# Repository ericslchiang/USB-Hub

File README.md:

## CHIP-8 Emulator by ericslchiang
### March 18th 2025  

######
An USB 2.0 Hub with three downstream USB 2.0 Ports and one SD card slot. Built using a Microchip USB2514B for USB Hub control and a Genesys Logic GL823K USB 2.0 to SD card converter IC.  
Routed on a 4-layer PCB with controlled impedances and length controlled USB differential routes. All design files in KiCAD.

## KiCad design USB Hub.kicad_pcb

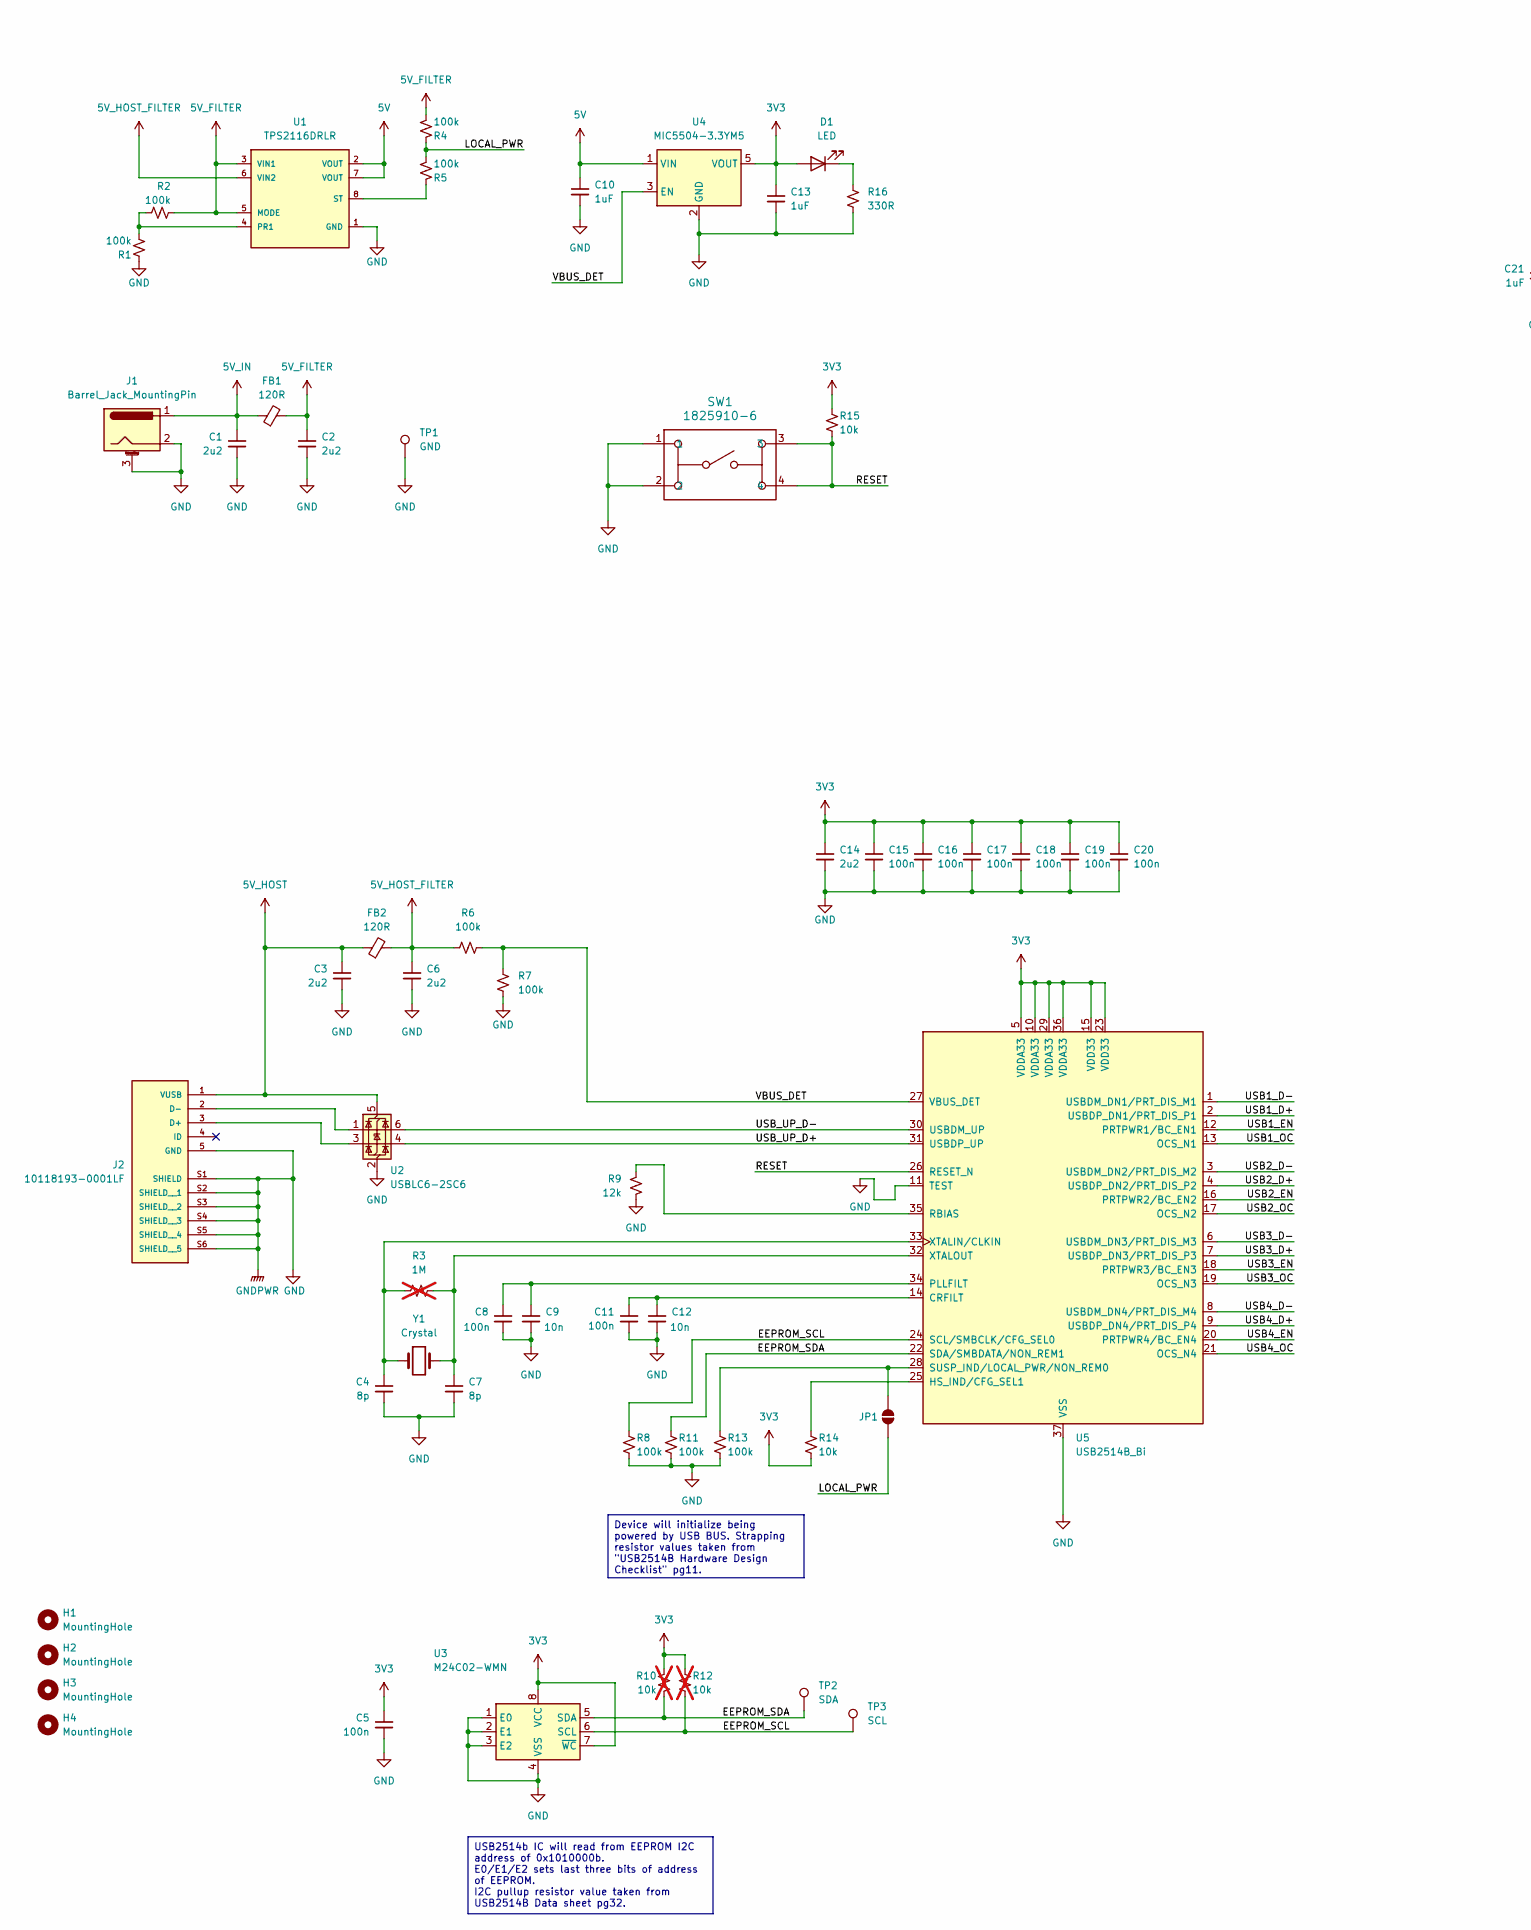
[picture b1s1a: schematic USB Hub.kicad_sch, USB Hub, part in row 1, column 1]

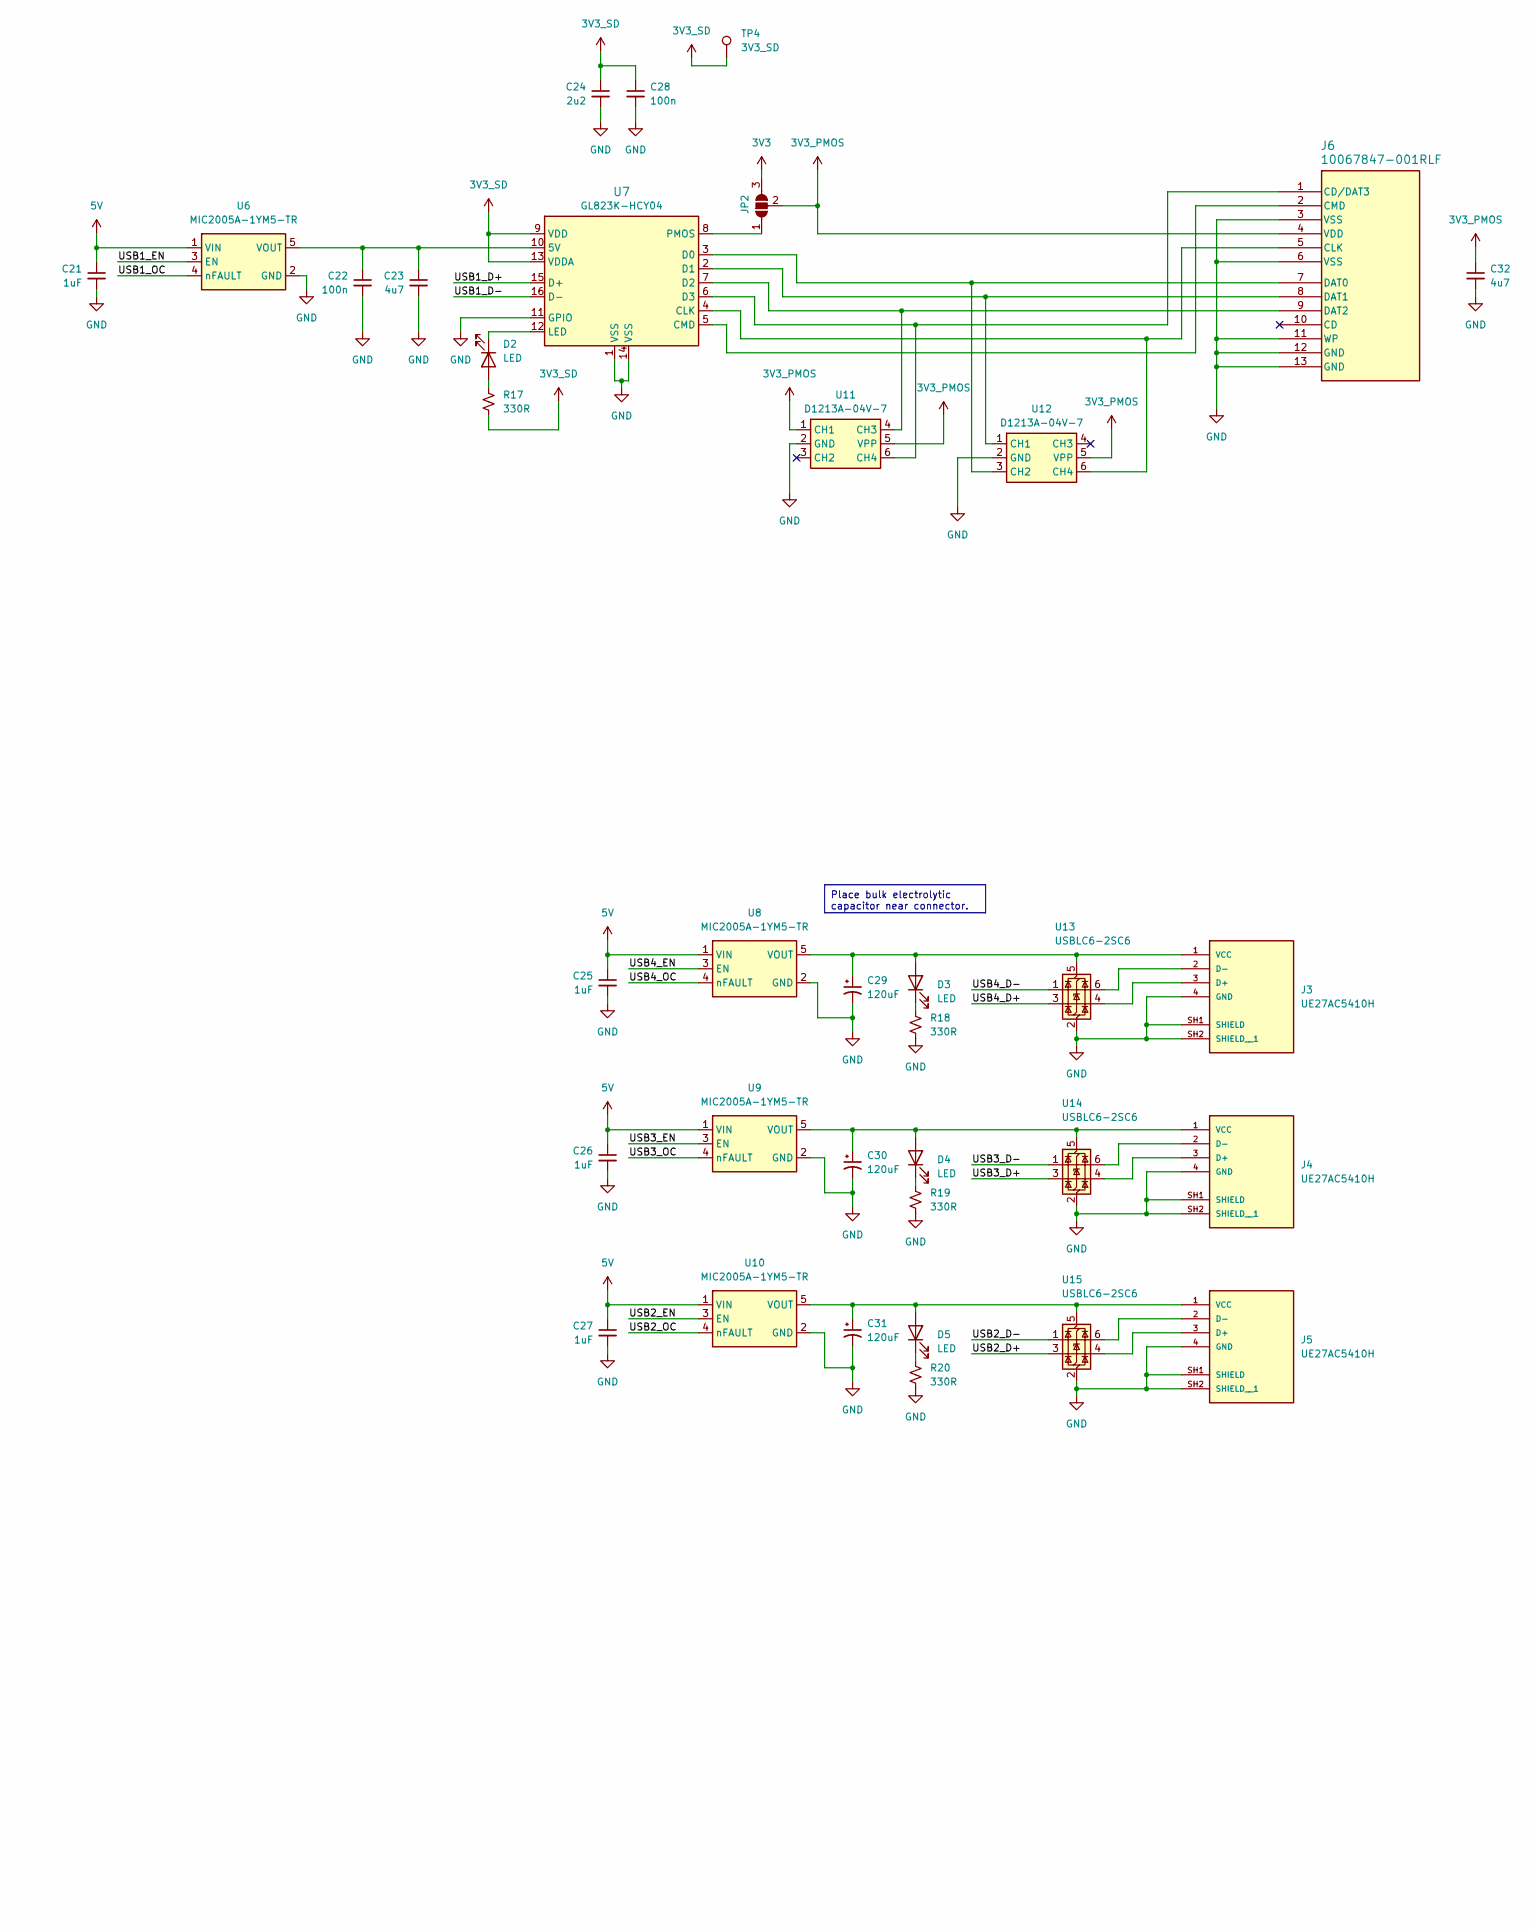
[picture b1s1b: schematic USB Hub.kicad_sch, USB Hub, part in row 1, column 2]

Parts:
C1, C2, C3, C6, C14, C24: 2u2; C_0805_2012Metric_Pad1.18x1.45mm_HandSolder
C4, C7: 8p; C_0603_1608Metric_Pad1.08x0.95mm_HandSolder
C5, C8, C11, C15, C16, C17, C18, C19, C20, C22, C28: 100n; C_0805_2012Metric_Pad1.18x1.45mm_HandSolder
C9, C12: 10n; C_0805_2012Metric_Pad1.18x1.45mm_HandSolder
C10, C13, C21, C25, C26, C27: 1uF; C_0805_2012Metric_Pad1.18x1.45mm_HandSolder
C23, C32: 4u7; C_0805_2012Metric_Pad1.18x1.45mm_HandSolder
C29, C30, C31: 120uF; CP_Radial_D5.0mm_P2.00mm
D1, D2, D3, D4, D5: LED; LED_0603_1608Metric_Pad1.05x0.95mm_HandSolder
FB1, FB2: 120R; L_0805_2012Metric_Pad1.05x1.20mm_HandSolder
H1, H2, H3, H4: MountingHole; MountingHole_3.2mm_M3_DIN965_Pad
J1: Barrel_Jack_MountingPin; BarrelJack_GCT_DCJ200-10-A_Horizontal
J2: 10118193-0001LF; AMPHENOL_10118193-0001LF; PARTREV E
J3, J4, J5: UE27AC5410H; AMPHENOL_UE27AC5410H; PARTREV G
J6: 10067847-001RLF; 10067847-001RLF_AMP
JP1: SolderJumper-2_P1.3mm_Open_Pad1.0x1.5mm
JP2: SolderJumper_3_Open; SolderJumper-3_P2.0mm_Open_TrianglePad1.0x1.5mm_NumberLabels
R1, R2, R4, R5, R6, R7, R8, R11, R13: 100k; R_0805_2012Metric_Pad1.20x1.40mm_HandSolder
R3: 1M; R_0805_2012Metric; not fitted
R9: 12k; R_0805_2012Metric_Pad1.20x1.40mm_HandSolder
R10, R12: 10k; R_0805_2012Metric_Pad1.20x1.40mm_HandSolder; not fitted
R14, R15: 10k; R_0805_2012Metric_Pad1.20x1.40mm_HandSolder
R16, R17, R18, R19, R20: 330R; R_0805_2012Metric_Pad1.20x1.40mm_HandSolder
SW1: 1825910-6; SW4_1825910-B_TEC
TP1: GND; TestPoint_THTPad_D4.0mm_Drill2.0mm
TP2: SDA; TestPoint_THTPad_2.0x2.0mm_Drill1.0mm
TP3: SCL; TestPoint_THTPad_2.0x2.0mm_Drill1.0mm
TP4: 3V3_SD; TestPoint_THTPad_2.0x2.0mm_Drill1.0mm
U1: TPS2116DRLR; SOTFL50P160X60-8N; PARTREV A
U2, U13, U14, U15: USBLC6-2SC6; SOT-23-6
U3: M24C02-WMN; SOIC-8_3.9x4.9mm_P1.27mm
U4: MIC5504-3.3YM5; SOT-23-5
U5: USB2514B_Bi; QFN-36-1EP_6x6mm_P0.5mm_EP3.7x3.7mm_ThermalVias
U6, U8, U9, U10: MIC2005A-1YM5-TR; SOT-23-5_HandSoldering
U7: GL823K-HCY04; SSOP-16_3.9x4.9mm_P0.635mm
U11, U12: D1213A-04V-7; SOT-563
Y1: Crystal; XTAL_HC49P488W43L1150T466H350

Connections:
3V3: C5.1, C13.1, C14.1, C15.1, C16.1, C17.1, C18.1, C19.1, C20.1, D1.2 (A), JP2.3 (B), R10.1, R12.1, R14.2, R15.1, U3.7 (~WC), U3.8 (VCC), U4.5 (VOUT), U5.5 (VDDA33), U5.10 (VDDA33), U5.15 (VDD33), U5.23 (VDD33), U5.29 (VDDA33), U5.36 (VDDA33)
3V3_PMOS: C32.1, J6.4 (VDD), JP2.2 (C), U11.1 (CH1), U11.5 (VPP), U12.5 (VPP)
3V3_SD: C24.1, C28.1, R17.1, TP4.1, U7.9 (VDD), U7.13 (VDDA)
5V: C10.1, C21.1, C25.1, C26.1, C27.1, U1.2 (VOUT), U1.7 (VOUT), U4.1 (VIN), U6.1 (VIN), U8.1 (VIN), U9.1 (VIN), U10.1 (VIN)
5V_FILTER: C2.1, FB1.2, R2.2, R4.2, U1.3 (VIN1), U1.5 (MODE)
5V_HOST: C3.1, FB2.1, J2.1 (VUSB), U2.5 (VBUS)
5V_HOST_FILTER: C6.1, FB2.2, R6.2, U1.6 (VIN2)
5V_IN: C1.1, FB1.1, J1.1
/EEPROM_SCL: R8.1, R12.2, TP3.1, U3.6 (SCL), U5.24 (SCL/SMBCLK/CFG_SEL0)
/EEPROM_SDA: R10.2, R11.1, TP2.1, U3.5 (SDA), U5.22 (SDA/SMBDATA/NON_REM1)
/LOCAL_PWR: JP1.1 (A), R4.1, R5.2
/RESET: R15.2, SW1.3, SW1.4, U5.26 (RESET_N)
/USB1_D+: U5.2 (USBDP_DN1/PRT_DIS_P1), U7.15 (D+)
/USB1_D-: U5.1 (USBDM_DN1/PRT_DIS_M1), U7.16 (D-)
/USB1_EN: U5.12 (PRTPWR1/BC_EN1), U6.3 (EN)
/USB1_OC: U5.13 (OCS_N1), U6.4 (nFAULT)
/USB2_D+: U5.4 (USBDP_DN2/PRT_DIS_P2), U15.3 (I/O2)
/USB2_D-: U5.3 (USBDM_DN2/PRT_DIS_M2), U15.1 (I/O1)
/USB2_EN: U5.16 (PRTPWR2/BC_EN2), U10.3 (EN)
/USB2_OC: U5.17 (OCS_N2), U10.4 (nFAULT)
/USB3_D+: U5.7 (USBDP_DN3/PRT_DIS_P3), U14.3 (I/O2)
/USB3_D-: U5.6 (USBDM_DN3/PRT_DIS_M3), U14.1 (I/O1)
/USB3_EN: U5.18 (PRTPWR3/BC_EN3), U9.3 (EN)
/USB3_OC: U5.19 (OCS_N3), U9.4 (nFAULT)
/USB4_D+: U5.9 (USBDP_DN4/PRT_DIS_P4), U13.3 (I/O2)
/USB4_D-: U5.8 (USBDM_DN4/PRT_DIS_M4), U13.1 (I/O1)
/USB4_EN: U5.20 (PRTPWR4/BC_EN4), U8.3 (EN)
/USB4_OC: U5.21 (OCS_N4), U8.4 (nFAULT)
/USB_UP_D+: U2.4 (I/O2), U5.31 (USBDP_UP)
/USB_UP_D-: U2.6 (I/O1), U5.30 (USBDM_UP)
/VBUS_DET: R6.1, R7.1, U4.3 (EN), U5.27 (VBUS_DET)
GND: C1.2, C2.2, C3.2, C4.2, C5.2, C6.2, C7.2, C8.2, C9.2, C10.2, C11.2, C12.2, C13.2, C14.2, C15.2, C16.2, C17.2, C18.2, C19.2, C20.2, C21.2, C22.2, C23.2, C24.2, C25.2, C26.2, C27.2, C28.2, C29.2, C30.2, C31.2, C32.2, J1.2, J1.3 (MountPin), J2.5 (GND), J2.S1 (SHIELD), J2.S2 (SHIELD__1), J2.S3 (SHIELD__2), J2.S4 (SHIELD__3), J2.S5 (SHIELD__4), J2.S6 (SHIELD__5), J3.4 (GND), J3.SH1 (SHIELD), J3.SH2 (SHIELD__1), J4.4 (GND), J4.SH1 (SHIELD), J4.SH2 (SHIELD__1), J5.4 (GND), J5.SH1 (SHIELD), J5.SH2 (SHIELD__1), J6.3 (VSS), J6.6 (VSS), J6.11 (WP), J6.12 (GND), J6.13 (GND), R1.1, R7.2, R8.2, R9.1, R11.2, R13.2, R16.1, R18.1, R19.1, R20.1, SW1.1, SW1.2, TP1.1, U1.1 (GND), U2.2 (GND), U3.1 (E0), U3.2 (E1), U3.3 (E2), U3.4 (VSS), U4.2 (GND), U5.11 (TEST), U5.37 (VSS), U6.2 (GND), U7.1 (VSS), U7.11 (GPIO), U7.14 (VSS), U8.2 (GND), U9.2 (GND), U10.2 (GND), U11.2 (GND), U12.2 (GND), U13.2 (GND), U14.2 (GND), U15.2 (GND)
unnamed: D1.1 (K), R16.2
unnamed: D2.2 (A), R17.2
unnamed: D2.1 (K), U7.12 (LED)
unnamed: C29.1, D3.2 (A), J3.1 (VCC), U8.5 (VOUT), U13.5 (VBUS)
unnamed: D3.1 (K), R18.2
unnamed: C30.1, D4.2 (A), J4.1 (VCC), U9.5 (VOUT), U14.5 (VBUS)
unnamed: D4.1 (K), R19.2
unnamed: C31.1, D5.2 (A), J5.1 (VCC), U10.5 (VOUT), U15.5 (VBUS)
unnamed: D5.1 (K), R20.2
unnamed: J2.3 (D+), U2.3 (I/O2)
unnamed: J2.2 (D-), U2.1 (I/O1)
unnamed: J3.3 (D+), U13.4 (I/O2)
unnamed: J3.2 (D-), U13.6 (I/O1)
unnamed: J4.3 (D+), U14.4 (I/O2)
unnamed: J4.2 (D-), U14.6 (I/O1)
unnamed: J5.3 (D+), U15.4 (I/O2)
unnamed: J5.2 (D-), U15.6 (I/O1)
unnamed: J6.1 (CD/DAT3), U7.6 (D3), U11.6 (CH4)
unnamed: J6.5 (CLK), U7.4 (CLK), U12.6 (CH4)
unnamed: J6.2 (CMD), U7.5 (CMD)
unnamed: J6.7 (DAT0), U7.3 (D0), U12.3 (CH2)
unnamed: J6.8 (DAT1), U7.2 (D1), U12.1 (CH1)
unnamed: J6.9 (DAT2), U7.7 (D2), U11.4 (CH3)
unnamed: JP1.2 (B), R13.1, U5.28 (SUSP_IND/LOCAL_PWR/NON_REM0)
unnamed: JP2.1 (A), U7.8 (PMOS)
unnamed: R1.2, R2.1, U1.4 (PR1)
unnamed: R5.1, U1.8 (ST)
unnamed: C11.1, C12.1, U5.14 (CRFILT)
unnamed: R14.1, U5.25 (HS_IND/CFG_SEL1)
unnamed: C8.1, C9.1, U5.34 (PLLFILT)
unnamed: R9.2, U5.35 (RBIAS)
unnamed: C4.1, R3.1, U5.33 (XTALIN/CLKIN), Y1.1
unnamed: C7.1, R3.2, U5.32 (XTALOUT), Y1.2
unnamed: C22.1, C23.1, U6.5 (VOUT), U7.10 (5V)

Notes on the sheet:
Device will initialize being powered by USB BUS. Strapping resistor values taken from "USB2514B Hardware Design Checklist" pg11.
USB2514b IC will read from EEPROM I2C address of 0x1010000b. E0/E1/E2 sets last three bits of address of EEPROM. I2C pullup resistor value taken from USB2514B Data sheet pg32.
Place bulk electrolytic capacitor near connector.

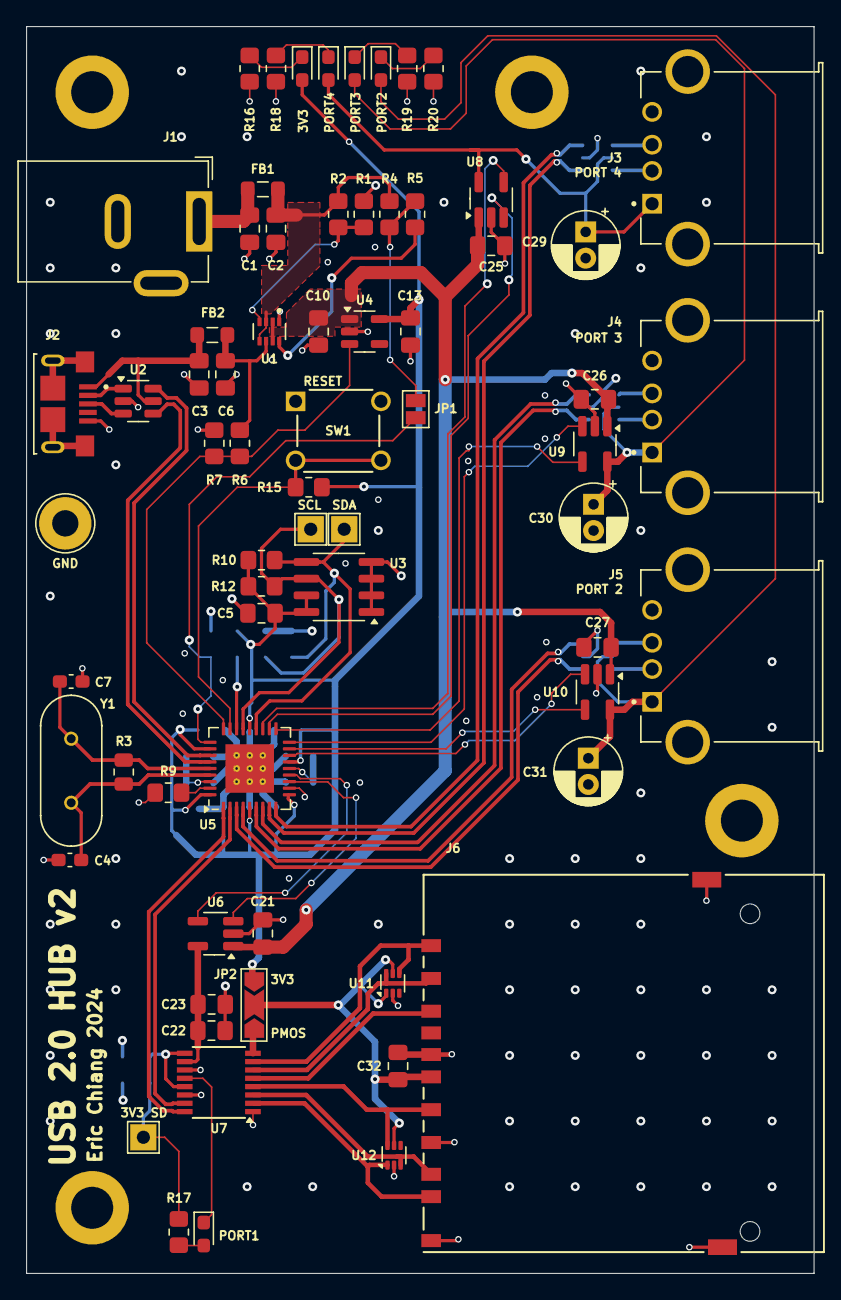
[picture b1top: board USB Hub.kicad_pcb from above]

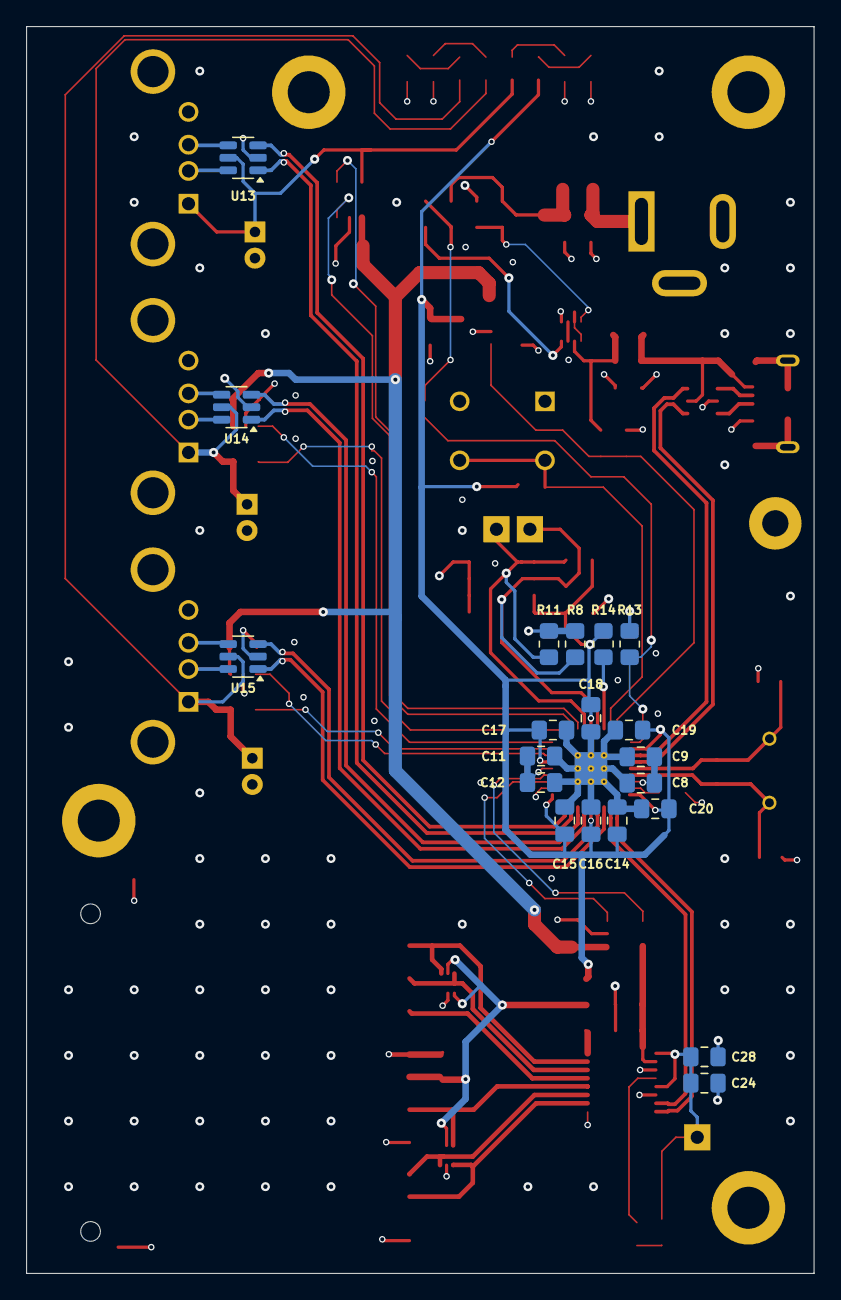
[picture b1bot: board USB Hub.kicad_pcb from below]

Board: 4 copper layers, 60.0 x 95.0 mm, 92 parts (20 on the bottom side), 66 nets.

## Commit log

2024-09-10 First revision of schematic
2024-09-15 first layout revision + some schematic rearrangements
2024-09-15 Fixed reference designator silkscreen and add copper pours to power section
2024-09-16 Fixed via stitching and sizes
2024-10-21 v2 of USB Hub
2025-09-13 Added readme
